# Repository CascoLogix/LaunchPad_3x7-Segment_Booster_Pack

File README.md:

# LaunchPad_3x7-Segment_Booster_Pack

#Description
This is just a simple 3x7-segment display that can be plugged into the TI MSP430 

#Background Info
I wanted to make my own 7-segment LED display booster pack for the LaunchPad that doesn't use a display driver IC, such as the CD4056BE, or SN7446A. In other words, I wanted to be in control of the firmware to perform driving the segments of each digit and performing the digit scanning function. 
So, I came up with this nifty little board - very simple. It includes a buffer driver IC, since the MSP430 IO pins are not rated to drive this much current in total. 
It was also a learning exercise, in that it was the first project where I used KiCAD's EDA software to learn all the ins and outs of creating schematic decals, PCB footprints, working with the component library interface, maping the schematic decals to the PCB footprints. And for the finishing touch, using Wings3D for creating the solid rendering of the boards. It was fun, easy, and it worked and I learned a lot in the process. 
Checkout the video in the links section below to see it in action!

#Links
##CascoLogix Product Page:
http://www.cascologix.com/store/p3/LaunchPad%C2%A03x7-segment_Booster_Pack.html
##Tindie Product Page:
https://www.tindie.com/products/CascoLogix/msp430-launchpad-3x7-segment-booster-pack/
##Hackaday Project Page:
https://hackaday.io/project/1779-launchpad-3x7-segment-display-booster-pack
##OSHPark PCB Page
https://oshpark.com/shared_projects/FeiOSTLi
##Video
https://www.youtube.com/watch?v=f7Dp6MClfQ0

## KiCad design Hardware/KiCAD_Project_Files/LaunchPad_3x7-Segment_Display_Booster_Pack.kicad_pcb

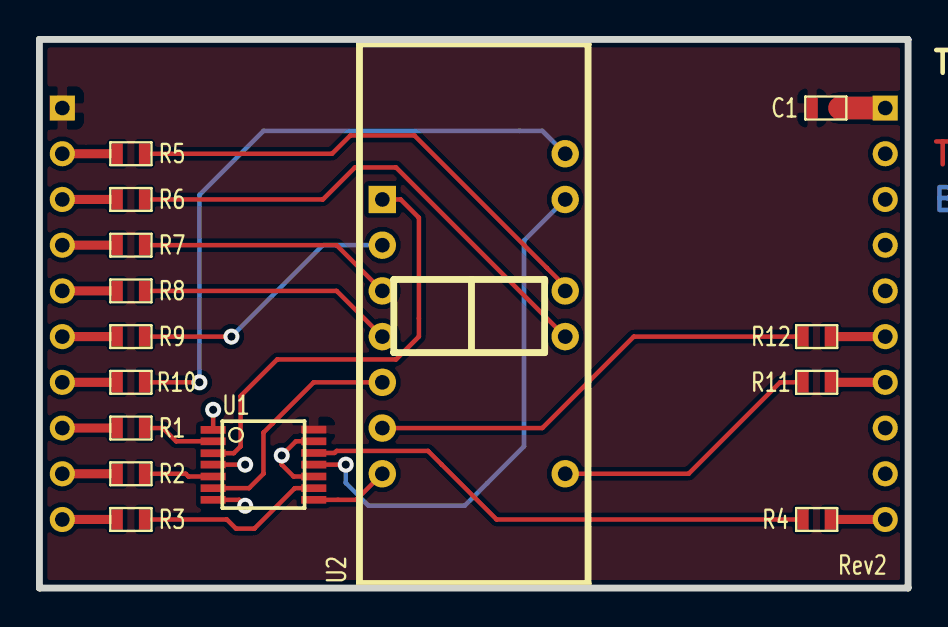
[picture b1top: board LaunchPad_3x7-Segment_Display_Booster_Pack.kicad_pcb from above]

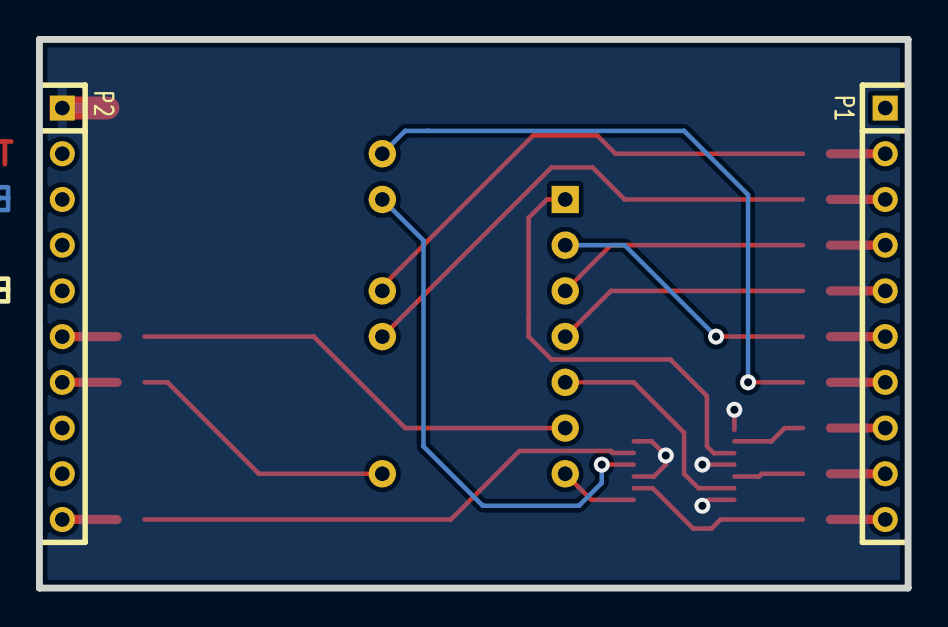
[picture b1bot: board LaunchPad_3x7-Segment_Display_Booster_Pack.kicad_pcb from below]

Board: 2 copper layers, 48.3 x 30.5 mm, 17 parts (2 on the bottom side), 30 nets.

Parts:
C1: 10uF; SM0603
P1, P2: HEADER_1X10; SIL-10
R1, R2, R3, R4, R5, R6, R7, R8, R9, R10, R11, R12: RES; SM0603
U1: 74LS125; SSOP14
U2: LTC4624; LTC4624JF

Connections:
+3.3V: C1.1, P1.1, U1.14
/SEG_A: P1.2, R5.2
/SEG_B: P1.3, R6.2
/SEG_C: P1.4, R7.2
/SEG_D: P1.5, R8.2
/SEG_DP: P2.6, R12.2
/SEG_E: P1.6, R9.2
/SEG_F: P1.7, R10.2
/SEG_G: P2.7, R11.2
GND: C1.2, P2.1, U1.1, U1.4, U1.7, U1.10, U1.13
unnamed: R1.1, U1.2
unnamed: R2.1, U1.5
unnamed: R3.1, U1.9
unnamed: P2.10, R4.1
unnamed: R5.1, U2.12
unnamed: R7.1, U2.3
unnamed: R9.1, U2.2
unnamed: R11.1, U2.8
unnamed: U1.11, U2.14
unnamed: R4.2, U1.12
unnamed: U1.8, U2.7
unnamed: U1.6, U2.5
unnamed: U1.3, U2.1
unnamed: R10.1, U2.15
unnamed: R8.1, U2.4
unnamed: R6.1, U2.11
unnamed: P1.8, R1.2
unnamed: P1.9, R2.2
unnamed: P1.10, R3.2
unnamed: R12.1, U2.6

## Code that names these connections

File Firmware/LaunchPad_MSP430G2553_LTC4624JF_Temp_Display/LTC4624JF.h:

#ifndef LTC4624JF_H_
#define LTC4624JF_H_


// Includes
#include <config.h>
#include <stdint.h>


// Defines
#define _COMMON_ANODE_

#define NUM_DIGITS 		3
#define NUM_ANODES		4

#define MAX_DECIMAL		10
#define MAX_HEXADECIMAL	16

#define ANODE_1			0
#define ANODE_2			1
#define ANODE_3			2
#define ANODE_4			3

#define DIGIT_1			ANODE_1
#define DIGIT_2			ANODE_2
#define DIGIT_3			ANODE_3
#define L_GROUP			ANODE_4

#define SEG_A			(1 << 0)
#define SEG_B			(1 << 1)
#define SEG_C			(1 << 2)
#define SEG_D			(1 << 3)
#define SEG_E			(1 << 4)
#define SEG_F			(1 << 5)
#define SEG_G			(1 << 6)
#define SEG_DP			(1 << 7)

#define SEG_L1			SEG_A
#define SEG_L2			SEG_B
#define SEG_L3			SEG_C


extern void WriteToDisplay(uint8_t alphaNumeric, uint8_t anode);
extern void TestDisplay(void);
extern void ClearDisplay(void);
extern void TestAnode(uint8_t anode);
extern void ClearAnode(uint8_t anode);
extern void DisplaySegments(void);
extern uint8_t DecimalNumLookup(uint8_t number);
extern uint8_t HexNumLookup(uint8_t number);
extern uint8_t AlphaLookup(char ascii);
extern void DPOn(uint8_t anode);
extern void DPOff(uint8_t anode);


extern uint8_t codedDataArray[NUM_ANODES];				// stores the active segments for each digit
extern uint8_t anode;									// local variable to select which anode is active
extern uint8_t testMode;								// local flag to activate/deactivate test mode


#endif /*LTC4624JF_H_*/

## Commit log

2013-01-26 First commit.
2013-01-26 Updated to current board design
2013-01-26 Reorganized directory to move gerber directory where it belongs.
2013-01-26 Updated resistor component values on schematic Updated pdf of schematic Created new gerber files to the gerber directory
2013-01-26 Corrected board to show Rev2 (previous check-in showed Rev1). Regenerated new gerbers with Rev2 artwork. Added rendered pictures of PCB assembly
2013-01-26 Renamed gerber archive to include "Gerbers" in the filename
2013-10-21 Updated to new kicad board format. + Rendered pic + pdf of BOM
    Minor corrections to schematic.
2013-10-21 Updated .hgignore
2013-11-03 Added gerbers for OSH Park and re-structured gerber file folders
2013-12-04 Minor changes to schematic due to updtaed female header decal. Updated sheet size to standard 8.5x11. Moved BOM's and Schematic into respective folders to conform to newer project directory structure.
2014-02-21 Added new kicad pcb file formats. Added layer identification text to each layer. Added pdf's of layout, assembly, and fabrication
2014-02-21 Added separate Top and Bottom Assembly drawings. Updated board renders to have transparent background.
2015-10-27 Added LTC4624JF.h and LTC4624JF.c files and example CCS projects. Removed old gerber files and other old files.
